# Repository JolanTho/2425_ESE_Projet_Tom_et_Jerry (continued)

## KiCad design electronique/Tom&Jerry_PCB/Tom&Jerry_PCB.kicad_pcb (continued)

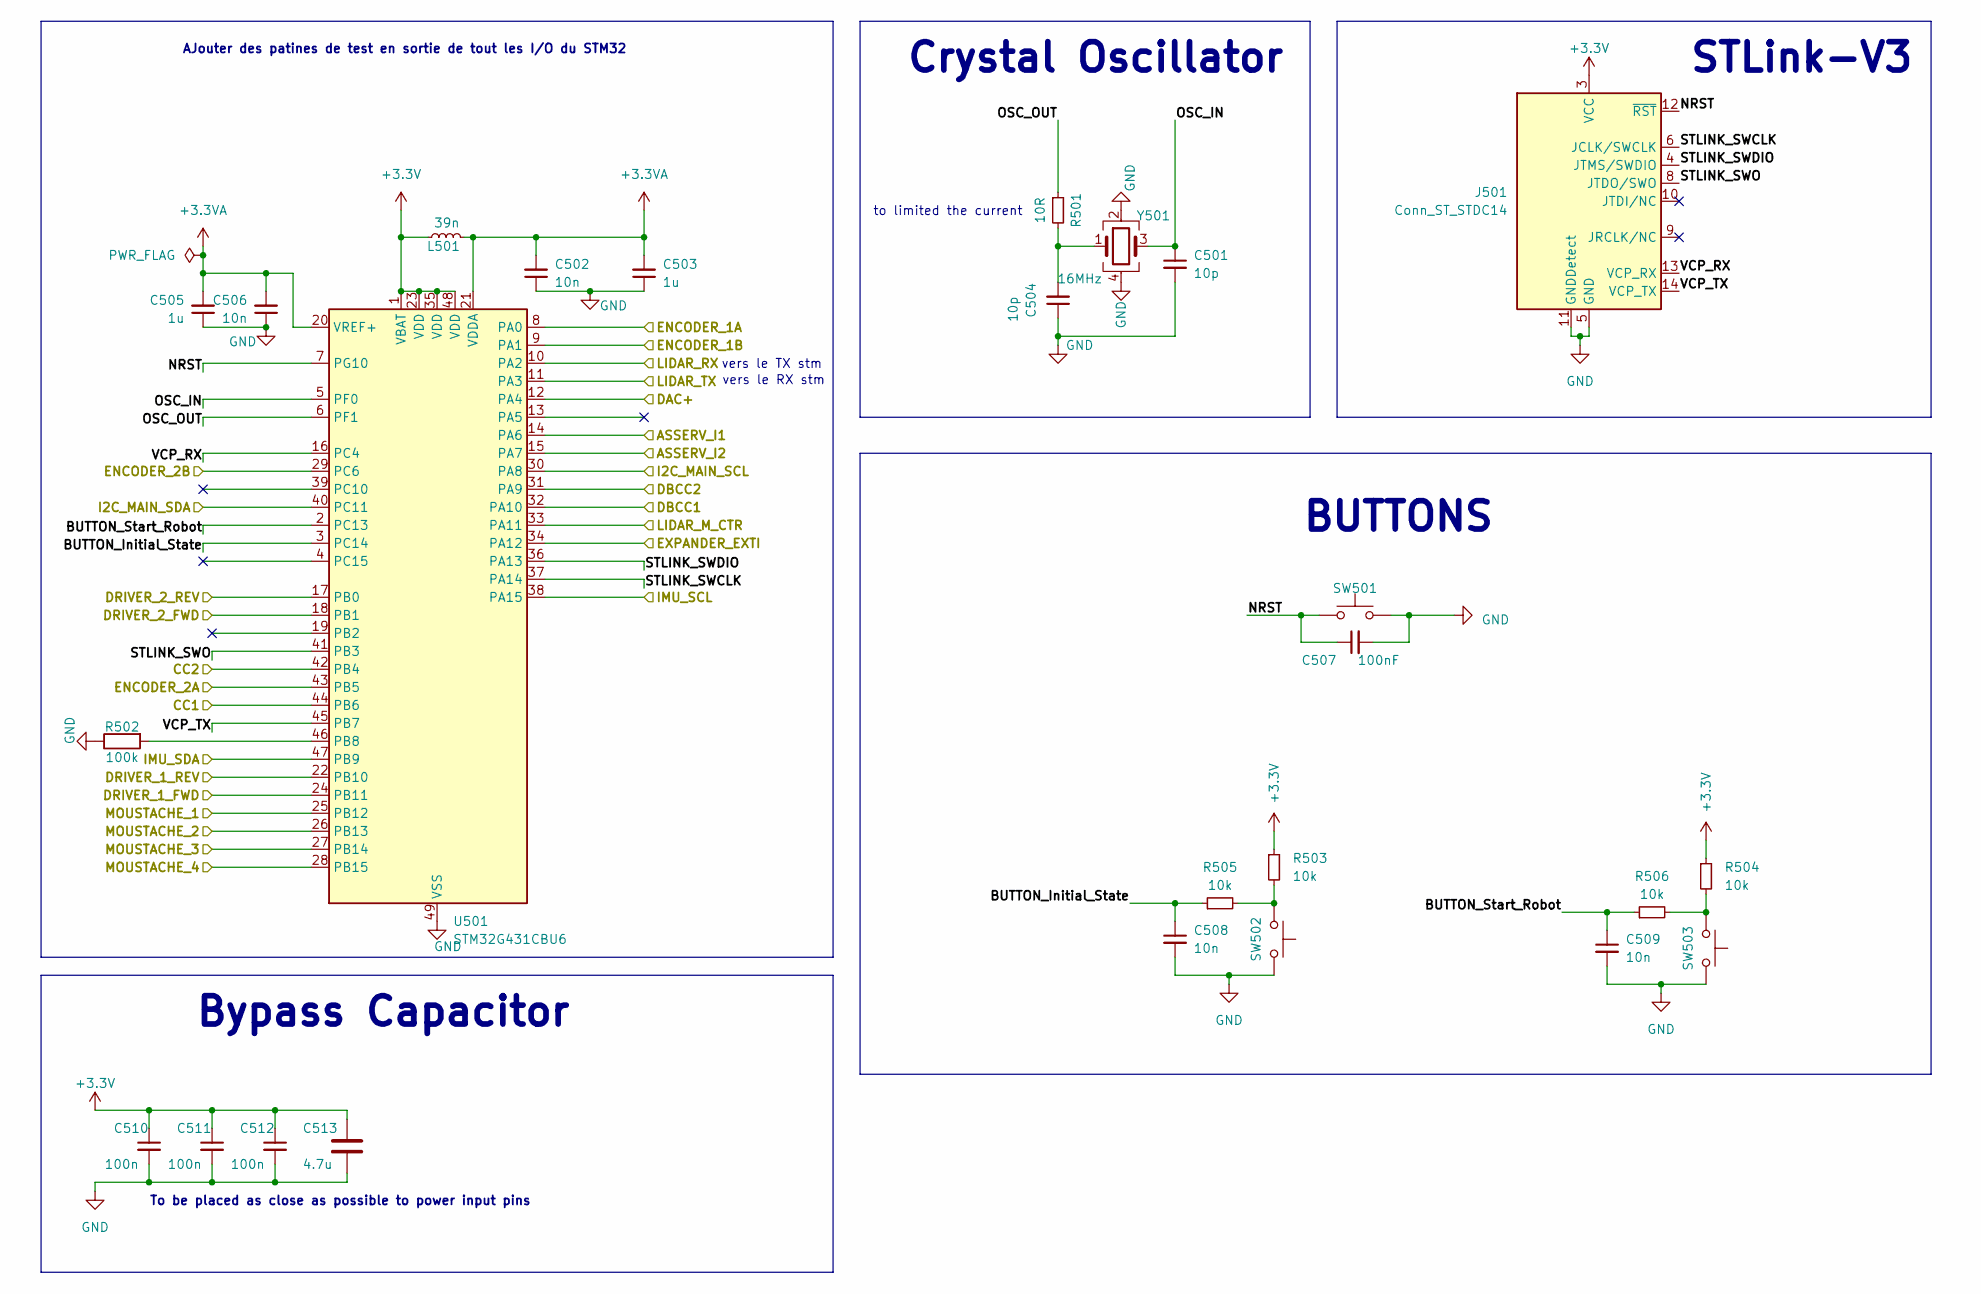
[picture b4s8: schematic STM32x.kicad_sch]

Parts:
C501, C504: 10p; C_0402_1005Metric
C502, C506, C508, C509: 10n; C_0402_1005Metric
C503, C505: 1u; C_0603_1608Metric
C507: 100nF; C_0402_1005Metric
C510, C511, C512: 100n; C_0402_1005Metric
C513: 4.7u; C_0603_1608Metric
J501: Conn_ST_STDC14; PinHeader_2x07_P1.27mm_Vertical_SMD
L501: 39n; WE-LQS_2512
R501: 10R; R_0402_1005Metric
R502: 100k; R_0402_1005Metric
R503, R504, R505, R506: 10k; R_0402_1005Metric
SW501, SW502, SW503: SW_Push; SW_Push_1P1T_NO_6x6mm_H9.5mm
U501: STM32G431CBU6; QFN-48-1EP_7x7mm_P0.5mm_EP5.1x5.1mm
Y501: 16MHz; Crystal_SMD_EuroQuartz_MT-4Pin_3.2x2.5mm; Mouser Part Number 2853935

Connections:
+3.3V: C510.1, C511.1, C512.1, C513.1, J501.3 (VCC), L501.2, R503.1, R504.1, U501.1 (VBAT), U501.23 (VDD), U501.35 (VDD), U501.48 (VDD); also elsewhere on the board
+3.3VA: C502.2, C503.2, C505.2, C506.2, L501.1, U501.20 (VREF+), U501.21 (VDDA)
/Alimentation/CC1: U501.32 (PA10), U501.44 (PB6); also elsewhere on the board
/Alimentation/CC2: U501.31 (PA9), U501.42 (PB4); also elsewhere on the board
/Led_Debug/Led_Debug_SCL: U501.30 (PA8); also elsewhere on the board
/Led_Debug/Led_Debug_SDA: U501.40 (PC11); also elsewhere on the board
/Motors&Drivers/ASSERV_I1: U501.14 (PA6); also elsewhere on the board
/Motors&Drivers/ASSERV_I2: U501.15 (PA7); also elsewhere on the board
/Motors&Drivers/ENCODER_1A: U501.8 (PA0); also elsewhere on the board
/Motors&Drivers/ENCODER_1B: U501.9 (PA1); also elsewhere on the board
/Motors&Drivers/ENCODER_2A: U501.43 (PB5); also elsewhere on the board
/Motors&Drivers/ENCODER_2B: U501.29 (PC6); also elsewhere on the board
/Motors&Drivers/PWM_MOT1_CH1: U501.24 (PB11); also elsewhere on the board
/Motors&Drivers/PWM_MOT1_CH2: U501.22 (PB10); also elsewhere on the board
/Motors&Drivers/PWM_MOT2_CH1: U501.18 (PB1); also elsewhere on the board
/Motors&Drivers/PWM_MOT2_CH2: U501.17 (PB0); also elsewhere on the board
/Musique/DAC_STM+: U501.12 (PA4); also elsewhere on the board
/Périphériques/EXPANDER_EXTI: U501.34 (PA12); also elsewhere on the board
/Périphériques/IMU_SCL: U501.38 (PA15); also elsewhere on the board
/Périphériques/IMU_SDA: U501.47 (PB9); also elsewhere on the board
/Périphériques/LIDAR_M_CTR: U501.33 (PA11); also elsewhere on the board
/Périphériques/LIDAR_RX: U501.10 (PA2); also elsewhere on the board
/Périphériques/LIDAR_TX: U501.11 (PA3); also elsewhere on the board
/Périphériques/MOUSTACHE_1: U501.25 (PB12); also elsewhere on the board
/Périphériques/MOUSTACHE_2: U501.26 (PB13); also elsewhere on the board
/Périphériques/MOUSTACHE_3: U501.27 (PB14); also elsewhere on the board
/Périphériques/MOUSTACHE_4: U501.28 (PB15); also elsewhere on the board
/STM32/BUTTON_Initial_State: C508.1, R505.1, U501.3 (PC14)
/STM32/BUTTON_Start_Robot: C509.1, R506.1, U501.2 (PC13)
/STM32/NRST: C507.1, J501.12 (~RST), SW501.1, U501.7 (PG10)
/STM32/OSC_IN: C501.1, U501.5 (PF0), Y501.3
/STM32/OSC_OUT: R501.1, U501.6 (PF1)
/STM32/STLINK_SWCLK: J501.6 (JCLK/SWCLK), U501.37 (PA14)
/STM32/STLINK_SWDIO: J501.4 (JTMS/SWDIO), U501.36 (PA13)
/STM32/STLINK_SWO: J501.8 (JTDO/SWO), U501.41 (PB3)
/STM32/VCP_RX: J501.13 (VCP_RX), U501.16 (PC4)
/STM32/VCP_TX: J501.14 (VCP_TX), U501.45 (PB7)
GND: C501.2, C502.1, C503.1, C504.1, C505.1, C506.1, C507.2, C508.2, C509.2, C510.2, C511.2, C512.2, C513.2, J501.5 (GND), J501.7 (GND), J501.11 (GNDDetect), R502.1, SW501.2, SW502.1, SW503.1, U501.49 (VSS), Y501.2, Y501.4; also elsewhere on the board
unnamed: C504.2, R501.2, Y501.1
unnamed: R503.2, R505.2, SW502.2
unnamed: R504.2, R506.2, SW503.2
unnamed: R502.2, U501.46 (PB8)

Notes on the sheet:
Bypass Capacitor
to limited the current
vers le TX stm
vers le RX stm
BUTTONS
AJouter des patines de test en sortie de tout les I/O du STM32
To be placed as close as possible to power input pins
Crystal Oscillator
STLink-V3

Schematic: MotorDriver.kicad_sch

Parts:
C1: 10uF; C_0603_1608Metric
C901: 100nF; C_0402_1005Metric
C902, C903, C904: 1uF; C_0603_1608Metric
IC901: NCS199A2RSQT2G; SOT65P210X110-6N; Mouser Part Number 863-NCS199A2RSQT2G
R901: 0.015; R_0805_2012Metric
U901: ZXBM5210-S; XBM5210; Mouser Part Number 621-ZXBM5210-SP-13

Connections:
1.65V: IC901.1 (REF); also elsewhere on the board
+3.3V: C901.1, IC901.3 (VS); also elsewhere on the board
+5V: C902.1, U901.3 (VDD), U901.6 (VREF); also elsewhere on the board
/Motors&Drivers/ASSERV_I1: IC901.6 (OUT); also elsewhere on the board
/Motors&Drivers/Motor1+: C903.1, IC901.5 (IN-), R901.2; also elsewhere on the board
/Motors&Drivers/Motor1-: C904.1, U901.7 (OUT2); also elsewhere on the board
/Motors&Drivers/PWM_MOT1_CH1: U901.4 (FWD); also elsewhere on the board
/Motors&Drivers/PWM_MOT1_CH2: U901.5 (REV); also elsewhere on the board
GND: C1.2, C901.2, C902.2, C903.2, C904.2, IC901.2 (GND), U901.8 (GND); also elsewhere on the board
unnamed: IC901.4 (IN+), R901.1, U901.1 (OUT1)
VCC: C1.1, U901.2 (VM); also elsewhere on the board

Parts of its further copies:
C2: 10uF; C_0603_1608Metric
C1101: 100nF; C_0402_1005Metric
C1102, C1103, C1104: 1uF; C_0603_1608Metric
IC1101: NCS199A2RSQT2G; SOT65P210X110-6N; Mouser Part Number 863-NCS199A2RSQT2G
R1101: 0.015; R_0805_2012Metric
U1101: ZXBM5210-S; XBM5210; Mouser Part Number 621-ZXBM5210-SP-13

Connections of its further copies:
1.65V: IC1101.1 (REF); also elsewhere on the board
+3.3V: C1101.1, IC1101.3 (VS); also elsewhere on the board
+5V: C1102.1, U1101.3 (VDD), U1101.6 (VREF); also elsewhere on the board
/Motors&Drivers/ASSERV_I2: IC1101.6 (OUT); also elsewhere on the board
/Motors&Drivers/Motor2+: C1103.1, IC1101.5 (IN-), R1101.2; also elsewhere on the board
/Motors&Drivers/Motor2-: C1104.1, U1101.7 (OUT2); also elsewhere on the board
/Motors&Drivers/PWM_MOT2_CH1: U1101.4 (FWD); also elsewhere on the board
/Motors&Drivers/PWM_MOT2_CH2: U1101.5 (REV); also elsewhere on the board
GND: C2.2, C1101.2, C1102.2, C1103.2, C1104.2, IC1101.2 (GND), U1101.8 (GND); also elsewhere on the board
unnamed: IC1101.4 (IN+), R1101.1, U1101.1 (OUT1)
VCC: C2.1, U1101.2 (VM); also elsewhere on the board

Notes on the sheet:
recommended capacitance is 100nF to 1μF
Gain 100
recommended capacitance is 100nF to 10μF
Shunt resistor

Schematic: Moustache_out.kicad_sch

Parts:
C1701: 10n; C_0402_1005Metric
J1701: Conn_01x02; JST_XH_S2B-XH-A-1_1x02_P2.50mm_Horizontal
R1701, R1702: 10k; R_0402_1005Metric

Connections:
+3.3V: R1701.1; also elsewhere on the board
/Périphériques/MOUSTACHE_4: C1701.1, R1702.1; also elsewhere on the board
GND: C1701.2, J1701.2; also elsewhere on the board
unnamed: J1701.1, R1701.2, R1702.2

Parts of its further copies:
C1301, C1501, C1601: 10n; C_0402_1005Metric
J1301, J1501, J1601: Conn_01x02; JST_XH_S2B-XH-A-1_1x02_P2.50mm_Horizontal
R1301, R1302, R1501, R1502, R1601, R1602: 10k; R_0402_1005Metric

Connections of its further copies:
+3.3V: R1301.1, R1501.1, R1601.1; also elsewhere on the board
/Périphériques/MOUSTACHE_1: C1301.1, R1302.1; also elsewhere on the board
/Périphériques/MOUSTACHE_2: C1501.1, R1502.1; also elsewhere on the board
/Périphériques/MOUSTACHE_3: C1601.1, R1602.1; also elsewhere on the board
GND: C1301.2, C1501.2, C1601.2, J1301.2, J1501.2, J1601.2; also elsewhere on the board
unnamed: J1301.1, R1301.2, R1302.2
unnamed: J1501.1, R1501.2, R1502.2
unnamed: J1601.1, R1601.2, R1602.2

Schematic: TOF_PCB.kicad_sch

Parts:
J1001: FTSH-105-01-F-DV-P-TR; SAMTEC_FTSH-105-01-F-DV-P-TR; PARTREV R

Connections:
+5V: J1001.05; also elsewhere on the board
/Led_Debug/Led_Debug_SCL: J1001.02; also elsewhere on the board
/Led_Debug/Led_Debug_SDA: J1001.04; also elsewhere on the board
/Périphériques/TOF1_GPIO1: J1001.03; also elsewhere on the board
/Périphériques/TOF1_XSHUT: J1001.01; also elsewhere on the board
/Périphériques/TOF2_GPIO1: J1001.09; also elsewhere on the board
/Périphériques/TOF2_XSHUT: J1001.07; also elsewhere on the board
/Périphériques/TOF3_GPIO1: J1001.10; also elsewhere on the board
/Périphériques/TOF3_XSHUT: J1001.08; also elsewhere on the board
GND: J1001.06; also elsewhere on the board

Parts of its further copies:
J701: FTSH-105-01-F-DV-P-TR; SAMTEC_FTSH-105-01-F-DV-P-TR; PARTREV R

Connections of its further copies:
+5V: J701.05; also elsewhere on the board
/Led_Debug/Led_Debug_SCL: J701.02; also elsewhere on the board
/Led_Debug/Led_Debug_SDA: J701.04; also elsewhere on the board
/Périphériques/TOF4_GPIO1: J701.03; also elsewhere on the board
/Périphériques/TOF4_XSHUT: J701.01; also elsewhere on the board
/Périphériques/TOF5_GPIO1: J701.09; also elsewhere on the board
/Périphériques/TOF5_XSHUT: J701.07; also elsewhere on the board
/Périphériques/TOF6_GPIO1: J701.10; also elsewhere on the board
/Périphériques/TOF6_XSHUT: J701.08; also elsewhere on the board
GND: J701.06; also elsewhere on the board

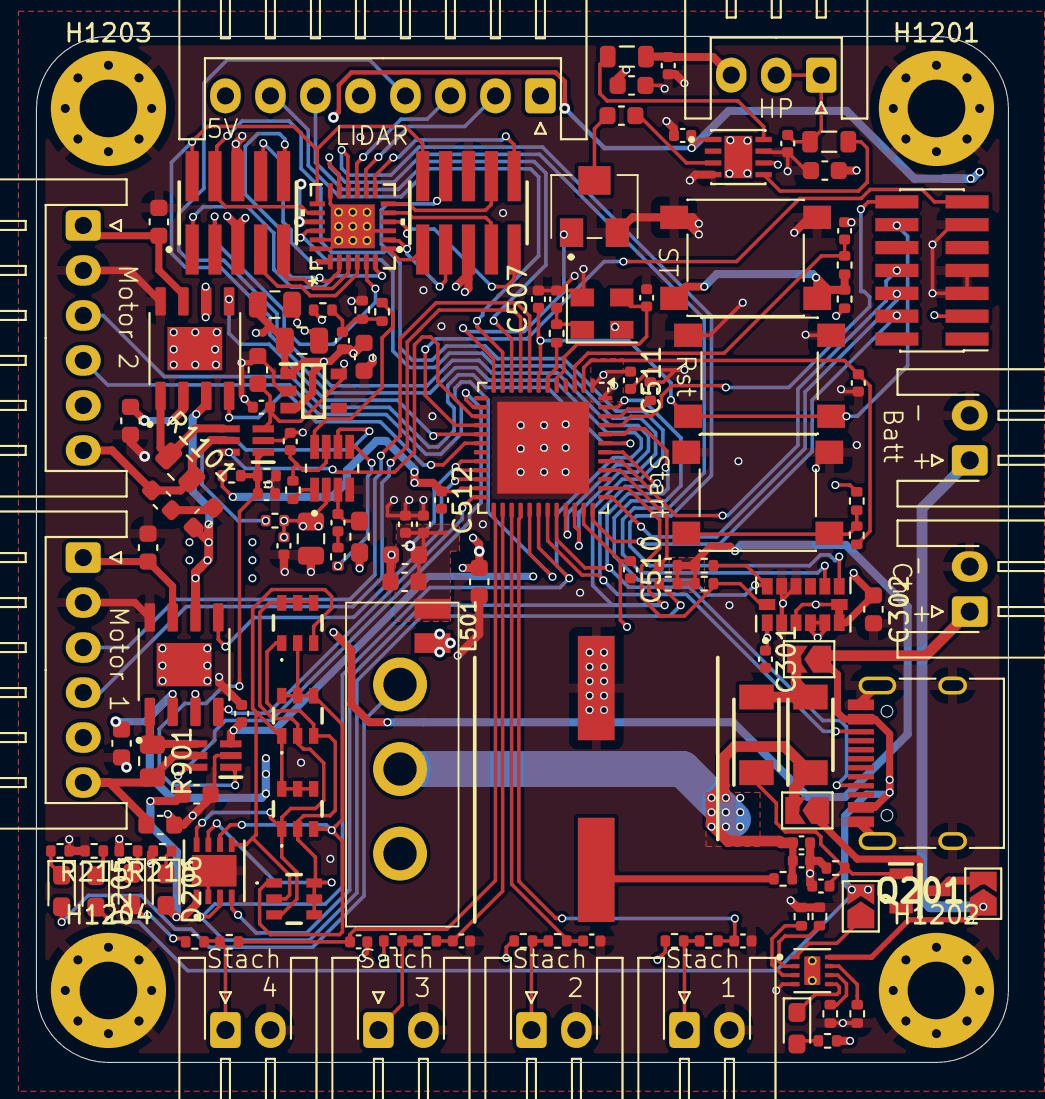
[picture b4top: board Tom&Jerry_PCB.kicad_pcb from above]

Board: 4 copper layers, 54.0 x 57.0 mm, 144 parts (0 on the bottom side), 108 nets.

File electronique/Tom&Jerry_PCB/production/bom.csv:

Designator,Footprint,Quantity,Value,LCSC Part #
"C1, C2",0603,2,10uF,
"C1101, C401, C507, C901",0402,4,100nF,
"C1102, C1103, C1104, C902, C903, C904",0603,6,1uF,
"C1301, C1501, C1601, C1701, C207, C211, C502, C506, C508, C509",0402,10,10n,
"C201, C203, C204",0805,3,22uF,
C202,0402,1,0.1u,
"C205, C209",0402,2,0.1uF,
"C206, C301, C510, C511, C512, C605",0402,6,100n,
C208,CAPAE1350X1400N,1,1mF,
C210,0402,1,15pF,
"C212, C213, C503, C505, C602, C604",0603,6,1u,
C302,0603,1,0.1u,
"C501, C504",0402,2,10p,
C513,0603,1,4.7u,
C601,0603,1,10u,
"C603, C606",0402,2,220p,
"D201, D202",SODFL4825X110N,2,D,
"D203, D204, D205, D206, D207",0603,5,LED,
"FB601, FB602",0805,2,FerriteBead_Small,
"IC1101, IC901",SOT65P210X110-6N,2,NCS199A2RSQT2G,
IC301,RTW24_2P45X2P45,1,TCA9555RTWR,
"J1001, J701",SAMTEC_FTSH-105-01-F-DV-P-TR,2,FTSH-105-01-F-DV-P-TR,
"J1301, J1501, J1601, J1701, J203, J204",JST_XH_S2B-XH-A-1_1x02_P2.50mm_Horizontal,6,Conn_01x02,
J201,Switch-3,1,Interrupteur,
J202,USB_C_Receptacle_HRO_TYPE-C-31-M-12,1,USB_C_Receptacle_USB2.0_16P,
J301,JST_XH_S8B-XH-A_1x08_P2.50mm_Horizontal,1,Conn_01x08,
"J401, J402",JST_XH_S6B-XH-A_1x06_P2.50mm_Horizontal,2,Conn_01x06,
J501,PinHeader_2x07_P1.27mm_Vertical_SMD,1,Conn_ST_STDC14,
J601,JST_XH_S3B-XH-A_1x03_P2.50mm_Horizontal,1,Conn_01x03,
L201,0603,1,4.7uH,
L501,0603,1,39n,
"LED801, LED802, LED803, LED804",5988G10313F,4,RGB,
PS201,SOT95P280X125-5N,1,BU33SD5WG-TR,
Q201,SOT95P237X112-3N,1,SI2365EDS-T1-GE3,
"R101, R102, R103, R104, R1301, R1302, R1501, R1502, R1601, R1602, R1701, R1702, R213, R503, R504, R505, R506",0402,17,10k,
"R1101, R901",0805,2,0.015,
R201,0402,1,20,
R202,0402,1,100m,
"R203, R204, R401, R402, R502",0402,5,100k,
R205,0402,1,16k,
R206,0402,1,40.2k,
R207,0402,1,7.68k,
R208,0402,1,15k,
"R209, R214, R215, R216, R217",0402,5,3.3k,
R210,0402,1,3.6k,
"R211, R212",0402,2,27k,
R501,0402,1,10R,
RV601,Potar,1,R_Potentiometer,
"SW501, SW502, SW503",SW_Push_1P1T_NO_6x6mm_H9.5mm,3,SW_Push,
"U1101, U901",XBM5210,2,ZXBM5210-S,
U201,SOT65P280X100-8N,1,MP1475DJ-LF-P,
U202,IC_BQ25172DSGR,1,BQ25172DSGR,
U301,PQFN80P300X500X100-14N,1,ADXL343,
U501,QFN-48-1EP_7x7mm_P0.5mm_EP5.1x5.1mm,1,STM32G431CBU6,
U601,DFN300X300X80-8N,1,PAM8302AAY,
U801,WSON8_DSD_TEX,1,LP5812ADSDR,
Y501,Crystal_SMD_EuroQuartz_MT-4Pin_3.2x2.5mm,1,16MHz,

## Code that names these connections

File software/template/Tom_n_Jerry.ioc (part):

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Mcu.Name=STM32G431C(6-8-B)Ux
Mcu.Package=UFQFPN48
Mcu.UserName=STM32G431CBUx
PA0.GPIOParameters=GPIO_Label
PA0.GPIO_Label=ENCODER_1B
PA0.Signal=S_TIM2_CH1
PA1.GPIOParameters=GPIO_Label
PA1.GPIO_Label=ENCODER_1A
PA1.Signal=S_TIM2_CH2
PA10.Mode=EnableDeadBattery
PA10.Signal=UCPD1_DBCC2
PA11.GPIOParameters=GPIO_Label
PA11.GPIO_Label=LIDAR_M_CTR
PA11.Signal=S_TIM4_CH1
PA13.Mode=Trace_Asynchronous_SW
PA13.Signal=SYS_JTMS-SWDIO
PA14.Mode=Trace_Asynchronous_SW
PA14.Signal=SYS_JTCK-SWCLK
PA15.GPIOParameters=GPIO_Label
PA15.GPIO_Label=I2C_IMU_SCL
PA15.Mode=I2C
PA15.Signal=I2C1_SCL
PA2.GPIOParameters=GPIO_Label
PA2.GPIO_Label=LIDAR_RXnTX_STM
PA2.Mode=Asynchronous
PA2.Signal=USART2_TX
PA3.GPIOParameters=GPIO_Label
PA3.GPIO_Label=LIDAR_TXnRX_STM
PA3.Mode=Asynchronous
PA3.Signal=USART2_RX
PA4.GPIOParameters=GPIO_Label
PA4.GPIO_Label=DAC+
PA4.Signal=COMP_DAC11_group
PA6.GPIOParameters=GPIO_Label
PA6.GPIO_Label=ASSERV_I1
PA6.Mode=IN3-Single-Ended
PA6.Signal=ADC2_IN3
PA7.GPIOParameters=GPIO_Label
PA7.GPIO_Label=ASSERV_I2
PA7.Mode=IN4-Single-Ended
PA7.Signal=ADC2_IN4
PA8.GPIOParameters=GPIO_Label
PA8.GPIO_Label=I2C_MAIN_SCL
PA8.Mode=I2C
PA8.Signal=I2C3_SCL
PA9.Mode=EnableDeadBattery
PA9.Signal=UCPD1_DBCC1
PB0.GPIOParameters=GPIO_Label
PB0.GPIO_Label=DRIVER_FWD2
PB0.Signal=S_TIM3_CH3
PB1.GPIOParameters=GPIO_Label
PB1.GPIO_Label=DRIVER_REV2
PB1.Signal=S_TIM3_CH4
PB10.GPIOParameters=GPIO_Label
PB10.GPIO_Label=DRIVER_REV1
PB10.Signal=S_TIM2_CH3
PB11.GPIOParameters=GPIO_Label
PB11.GPIO_Label=DRIVER_FWD1
PB11.Signal=S_TIM2_CH4
PB12.GPIOParameters=GPIO_Label
PB12.GPIO_Label=MOUSTACHE_4
PB12.Signal=GPXTI12
PB15.GPIOParameters=GPIO_Label
PB15.GPIO_Label=MOUSTACHE_1
PB15.Signal=GPXTI15
PB3.Mode=Trace_Asynchronous_SW
PB3.Signal=SYS_JTDO-SWO
PB4.Mode=Source_AllSignals
PB4.Signal=UCPD1_CC2
PB5.GPIOParameters=GPIO_Label
PB5.GPIO_Label=ENCODER_2B
PB5.Signal=S_TIM3_CH2
PB6.Mode=Source_AllSignals
PB6.Signal=UCPD1_CC1
PB7.GPIOParameters=GPIO_Label
PB7.GPIO_Label=VCP_RX
PB7.Mode=Asynchronous
PB7.Signal=USART1_RX
PB9.GPIOParameters=GPIO_Label
PB9.GPIO_Label=I2C_IMU_SDA
PB9.Mode=I2C
PB9.Signal=I2C1_SDA
PC11.GPIOParameters=GPIO_Label
PC11.GPIO_Label=I2C_MAIN_SDA
PC11.Mode=I2C
PC11.Signal=I2C3_SDA
PC13.GPIOParameters=GPIO_Label
PC13.GPIO_Label=BUTTON_INITIAL_STATE
PC13.Signal=GPXTI13
PC14-OSC32_IN.GPIOParameters=GPIO_Label
PC14-OSC32_IN.GPIO_Label=BUTTON_START_ROBOT
PC14-OSC32_IN.Signal=GPXTI14
PC4.GPIOParameters=GPIO_Label
PC4.GPIO_Label=VCP_TX
PC4.Mode=Asynchronous
PC4.Signal=USART1_TX
PC6.GPIOParameters=GPIO_Label
PC6.GPIO_Label=ENCODER_2A
PC6.Signal=S_TIM3_CH1
PF0-OSC_IN.Mode=HSE-External-Oscillator
PF0-OSC_IN.Signal=RCC_OSC_IN
PF1-OSC_OUT.Mode=HSE-External-Oscillator
PF1-OSC_OUT.Signal=RCC_OSC_OUT
RCC.HSE_VALUE=8000000
RCC.SYSCLKFreq_VALUE=16000000
board=custom

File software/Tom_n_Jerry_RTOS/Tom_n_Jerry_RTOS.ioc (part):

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Mcu.Name=STM32G431C(6-8-B)Ux
Mcu.Package=UFQFPN48
Mcu.UserName=STM32G431CBUx
PA10.Mode=EnableDeadBattery
PA10.Signal=UCPD1_DBCC2
PA11.GPIOParameters=PinState,GPIO_Label
PA11.GPIO_Label=LIDAR_M_CTR
PA11.PinState=GPIO_PIN_SET
PA11.Signal=GPIO_Output
PA12.GPIOParameters=GPIO_PuPd,GPIO_Label,GPIO_ModeDefaultEXTI
PA12.GPIO_Label=GE_EXTI
PA12.GPIO_ModeDefaultEXTI=GPIO_MODE_IT_RISING
PA12.GPIO_PuPd=GPIO_PULLUP
PA12.Signal=GPXTI12
PA13.Mode=Trace_Asynchronous_SW
PA13.Signal=SYS_JTMS-SWDIO
PA14.Mode=Trace_Asynchronous_SW
PA14.Signal=SYS_JTCK-SWCLK
PA15.GPIOParameters=GPIO_Label
PA15.GPIO_Label=I2C_IMU_SCL
PA15.Mode=I2C
PA15.Signal=I2C1_SCL
PA2.GPIOParameters=GPIO_Label
PA2.GPIO_Label=LIDAR_RXnTX_STM
PA2.Mode=Asynchronous
PA2.Signal=USART2_TX
PA3.GPIOParameters=GPIO_Label
PA3.GPIO_Label=LIDAR_TXnRX_STM
PA3.Mode=Asynchronous
PA3.Signal=USART2_RX
PA4.GPIOParameters=GPIO_Label
PA4.GPIO_Label=DAC+
PA4.Signal=COMP_DAC11_group
PA6.GPIOParameters=GPIO_Label
PA6.GPIO_Label=ASSERV_I1
PA6.Mode=IN3-Single-Ended
PA6.Signal=ADC2_IN3
PA7.GPIOParameters=GPIO_Label
PA7.GPIO_Label=ASSERV_I2
PA7.Mode=IN4-Single-Ended
PA7.Signal=ADC2_IN4
PA8.GPIOParameters=GPIO_Label
PA8.GPIO_Label=I2C_MAIN_SCL
PA8.Mode=I2C
PA8.Signal=I2C3_SCL
PA9.Mode=EnableDeadBattery
PA9.Signal=UCPD1_DBCC1
PB0.GPIOParameters=GPIO_Label
PB0.GPIO_Label=DRIVER_FWD2
PB0.Signal=S_TIM3_CH3
PB1.GPIOParameters=GPIO_Label
PB1.GPIO_Label=DRIVER_REV2
PB1.Signal=S_TIM3_CH4
PB10.GPIOParameters=GPIO_Label
PB10.GPIO_Label=DRIVER_REV1
PB10.Signal=S_TIM2_CH3
PB11.GPIOParameters=GPIO_Label
PB11.GPIO_Label=DRIVER_FWD1
PB11.Signal=S_TIM2_CH4
PB13.GPIOParameters=GPIO_Label
PB13.GPIO_Label=MOUSTACHE_3
PB13.Signal=GPIO_Input
PB14.GPIOParameters=GPIO_Label
PB14.GPIO_Label=START
PB14.Signal=GPXTI14
PB15.GPIOParameters=GPIO_Label
PB15.GPIO_Label=MOUSTACHE_1
PB15.Signal=GPIO_Input
PB3.Mode=Trace_Asynchronous_SW
PB3.Signal=SYS_JTDO-SWO
PB4.Mode=Sink_AllSignals
PB4.Signal=UCPD1_CC2
PB6.Mode=Sink_AllSignals
PB6.Signal=UCPD1_CC1
PB7.GPIOParameters=GPIO_Label
PB7.GPIO_Label=VCP_RX
PB7.Mode=Asynchronous
PB7.Signal=USART1_RX
PB9.GPIOParameters=GPIO_Label
PB9.GPIO_Label=I2C_IMU_SDA
PB9.Mode=I2C
PB9.Signal=I2C1_SDA
PC11.GPIOParameters=GPIO_Label
PC11.GPIO_Label=I2C_MAIN_SDA
PC11.Mode=I2C
PC11.Signal=I2C3_SDA
PC4.GPIOParameters=GPIO_Label
PC4.GPIO_Label=VCP_TX
PC4.Mode=Asynchronous
PC4.Signal=USART1_TX
PF0-OSC_IN.Mode=HSE-External-Oscillator
PF0-OSC_IN.Signal=RCC_OSC_IN
PF1-OSC_OUT.Mode=HSE-External-Oscillator
PF1-OSC_OUT.Signal=RCC_OSC_OUT
RCC.HSE_VALUE=8000000
RCC.SYSCLKFreq_VALUE=16000000
board=custom

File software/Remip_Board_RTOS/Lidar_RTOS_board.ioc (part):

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Mcu.Name=STM32G431R(6-8-B)Tx
Mcu.Package=LQFP64
Mcu.UserName=STM32G431RBTx
PA13.GPIOParameters=GPIO_Label
PA13.GPIO_Label=T_SWDIO
PA13.Mode=Serial_Wire
PA13.Signal=SYS_JTMS-SWDIO
PA14.GPIOParameters=GPIO_Label
PA14.GPIO_Label=T_SWCLK
PA14.Mode=Serial_Wire
PA14.Signal=SYS_JTCK-SWCLK
PA2.GPIOParameters=GPIO_Label
PA2.GPIO_Label=VCP_TX
PA2.Mode=Asynchronous
PA2.Signal=USART2_TX
PA3.GPIOParameters=GPIO_Label
PA3.GPIO_Label=VCP_RX
PA3.Mode=Asynchronous
PA3.Signal=USART2_RX
PA5.GPIOParameters=GPIO_Label
PA5.GPIO_Label=LD2 [green]
PA5.Signal=GPIO_Output
PB3.GPIOParameters=GPIO_Label
PB3.GPIO_Label=LIDAR_M_SCTR
PB3.Signal=S_TIM2_CH2
PB4.GPIOParameters=GPIO_Label
PB4.GPIO_Label=LIDAR_M_EN
PB4.Signal=GPIO_Output
PB5.GPIOParameters=GPIO_Label
PB5.GPIO_Label=LIDAR_DEV_EN
PB5.Signal=GPIO_Output
PC13.GPIOParameters=GPIO_Label
PC13.GPIO_Label=B1 [blue push button]
PC13.Signal=GPXTI13
PC14-OSC32_IN.GPIOParameters=GPIO_Label
PC14-OSC32_IN.GPIO_Label=RCC_OSC32_OUT
PC14-OSC32_IN.Signal=RCC_OSC32_IN
PC15-OSC32_OUT.GPIOParameters=GPIO_Label
PC15-OSC32_OUT.GPIO_Label=RCC_OSC32_OUT
PC15-OSC32_OUT.Signal=RCC_OSC32_OUT
PC4.GPIOParameters=GPIO_Label
PC4.GPIO_Label=LIDAR_RXnTX_STM
PC4.Mode=Asynchronous
PC4.Signal=USART1_TX
PC5.GPIOParameters=GPIO_Label
PC5.GPIO_Label=LIDAR_TXnTRX_STM
PC5.Mode=Asynchronous
PC5.Signal=USART1_RX
PF0-OSC_IN.GPIOParameters=GPIO_Label
PF0-OSC_IN.GPIO_Label=RCC_OSC_IN
PF0-OSC_IN.Mode=HSE-External-Oscillator
PF0-OSC_IN.Signal=RCC_OSC_IN
PF1-OSC_OUT.GPIOParameters=GPIO_Label
PF1-OSC_OUT.GPIO_Label=RCC_OSC_OUT
PF1-OSC_OUT.Mode=HSE-External-Oscillator
PF1-OSC_OUT.Signal=RCC_OSC_OUT
RCC.HSE_VALUE=24000000
RCC.SYSCLKFreq_VALUE=170000000
RCC.SYSCLKSource=RCC_SYSCLKSOURCE_PLLCLK
board=NUCLEO-G431RB
boardIOC=true

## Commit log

2024-09-11 Update README.md
    Ajout du squelette ReadMe.md
2024-09-13 Ajout draft shematique
2024-09-13 Correction problemes
2024-09-17 STM32 KiCAD V1
2024-09-18 Final_Review_Alimentation
2024-09-18 STM32 KiCAD V2 - 18.09.2024
2024-09-18 KiCAD V3 - 18.09.2024
2024-09-20 STM32 KiCAD V4 - 20.09.2024
2024-09-20 STM32 KiCAD V5 - 20.09.2024
2024-09-23 Ajout du Read.me de la partie alimentation
2024-09-23 STM32 Template v1(Pins Non-Assigned) - 23.09.2024
2024-09-23 gitignore - 23.09.2024
2024-09-24 ReadMe update and doc add
2024-09-25 Read.me + Docs
2024-09-25 Mise en page Read.me
2024-09-25 Test Read.me
2024-09-25 Tests liste de puces
2024-09-25 Update listes à puces
2024-09-25 New update listes à puces
2024-09-25 Nouvelle update
2024-09-25 Update Read.me en beau
2024-09-25 Update Read.me avec formalisme
2024-09-25 STM32 KiCAD V5 - 25.09.2024 - Ajout connecteurs TOF, ...
2024-09-25 STM32 KiCAD V6 - 25.09.2024 - Ajout des points test
2024-09-25 STM32 KiCAD V6 - 25.09.2024 - Nettoyage des mauvais pins
2024-09-25 STM32 KiCAD v7 x CubeIDE - Correction gpio_expander et driver gpio_expander
2024-10-01 Nettoyag .DS_Store
2024-10-01 STM32 KiCAD v2.0 x CubeIDE - Pin definitif + schematic reviewed
2024-10-02 .gitignore update
2024-10-02 Adding footprint V0.1
2024-10-02 Changing footprint V0.2
2024-10-04 Ajout des bonnes empreintes
2024-10-04 Ajout V2 TOF + MultiPCB Panalize
2024-10-05 Migration CubeIDE vers 1.16.1
2024-10-05 First try placement
2024-10-05 Try some placement and routing
2024-10-06 Ajout du routage LED + TOF + quelques Via
2024-10-06 Ajout des derniers via utiles
2024-10-07 Routage Signal Complet
2024-10-07 Routage Power
2024-10-07 Template update
2024-10-07 Test d'un pre-commit hooks pour clean tout les projets .ioc
2024-10-08 V2.0 placement avec tout dessus
    Aucun routage réalisé
2024-10-08 Lidar breadboard
2024-10-08 Routage Signal Complet - PCB V2.0
2024-10-08 Corrections mineures routage - PCB V2.0
2024-10-09 Lidar en DMA - ECHEC
2024-10-09 .gitignore
2024-10-09 Routage finish awaiting review PCB2.0
2024-10-09 Lidar mais plus en DMA - ECHEC
2024-10-16 Communication LIDAR IT - Début code propre
2024-10-16 c rémi qui m'a dit
    g écrit sur le PCB.
2024-10-17 Kicad - Deplacement des pins sous PASTE x empreinte MOSFET
2024-10-17 Nothing important, just an inchident
2024-10-21 Cleaning for PCB prof review
2024-10-21 Bidouille pour merge
2024-10-21 Mac c'est nul
    facile
2024-10-21 Mac c'est nul
2024-10-21 Correction erreurs PCB
2024-10-21 Cleaning
2024-10-22 little Update README.md
2024-10-22 Adding all files to critic error PCB
2024-10-23 Last commit before PCB command
2024-10-23 Generation des jlcpcb files
2024-10-23 Creating Remip board test
2024-10-23 Rshunt en 0603
2024-10-23 Ajout des freeRTOS Tom&Jerry x shell sur board
2024-10-23 Derniere modif jlcpcb
2024-11-06 changement mineure
2024-11-13 Minor changes in lidar
2024-11-17 EAZY PEAZY LEMON SQUEEZY
2024-11-20 MAJOR UPGRADE : cubeIDE rtos - multiple drivers work | MINOR UPGRADE : schematic correction (too late)| COMMIT BEFORE MULTIPLE TASKS CREATION
2024-11-26 Maj Lidar RTOS first data
2024-11-26 Major Changes Circular DMA V1
2024-11-26 Changement et MAJ des README electronique
2024-11-29 GPIOExpander + ADXL Single TAP + Mode Change : OK | Need Fine Tuned Single TAP
2024-12-06 Ajout de ka methode K_means
2024-12-11 MAJOR UPDATE | Intégration finale v0.1
2024-12-11 GPIO EXTI - Bord Detection : OK
2024-12-11 Chat en cours de miaulement
2024-12-13 Moteurs controlés par Lidar : OK (mode:chat only)
2024-12-23 Test Unitaire Moteur
2025-01-09 Commit ReadMe Elec V1
2025-01-09 ReadMe Lidar
2025-01-09 Update readme Software avec d'autrs composants
2025-01-10 Ajout bonne bobines + 3.3v gpio expander + Driver moteur
2025-01-10 VERSION VF.1|detection bord + suivi + courbe vitesse | 1ere intergation complete
2025-01-10 VERSION VF.1| Ajout d'un -v sur la commande angle pour eviter de flood le temrinal
